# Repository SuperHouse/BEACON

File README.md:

IR / RF Transmitter / Receiver Beacon with WiFi
===============================================
Copyright 2016 SuperHouse Automation Pty Ltd  www.superhouse.tv  

Transmitter and receiver for both IR (infra-red) and 433MHz RF signals.
Includes a footprint for a Spark Core or Particle Photon.

Features:

 * Particle Photon controller
 * 433MHz transmitter
 * 433MHz receiver
 * I/R transmitter
 * I/R receiver
 * Status LEDs

More information:

  http://www.superhouse.tv/beacon

INSTALLATION
------------
The design is saved as an EAGLE project. EAGLE PCB design software is
available from www.cadsoftusa.com free for non-commercial use. To use
this project download it and place the directory containing these files
into the "eagle" directory on your computer. Then open EAGLE and
navigate to the project.

CREDITS
-------
Designed by Jonathan Oxer jon@oxer.com.au

DISTRIBUTION
------------
The specific terms of distribution of this project are governed by the
license referenced below.

LICENSE
-------
Licensed under the TAPR Open Hardware License (www.tapr.org/OHL).
The "license" folder within this repository also contains a copy of
this license in plain text format.

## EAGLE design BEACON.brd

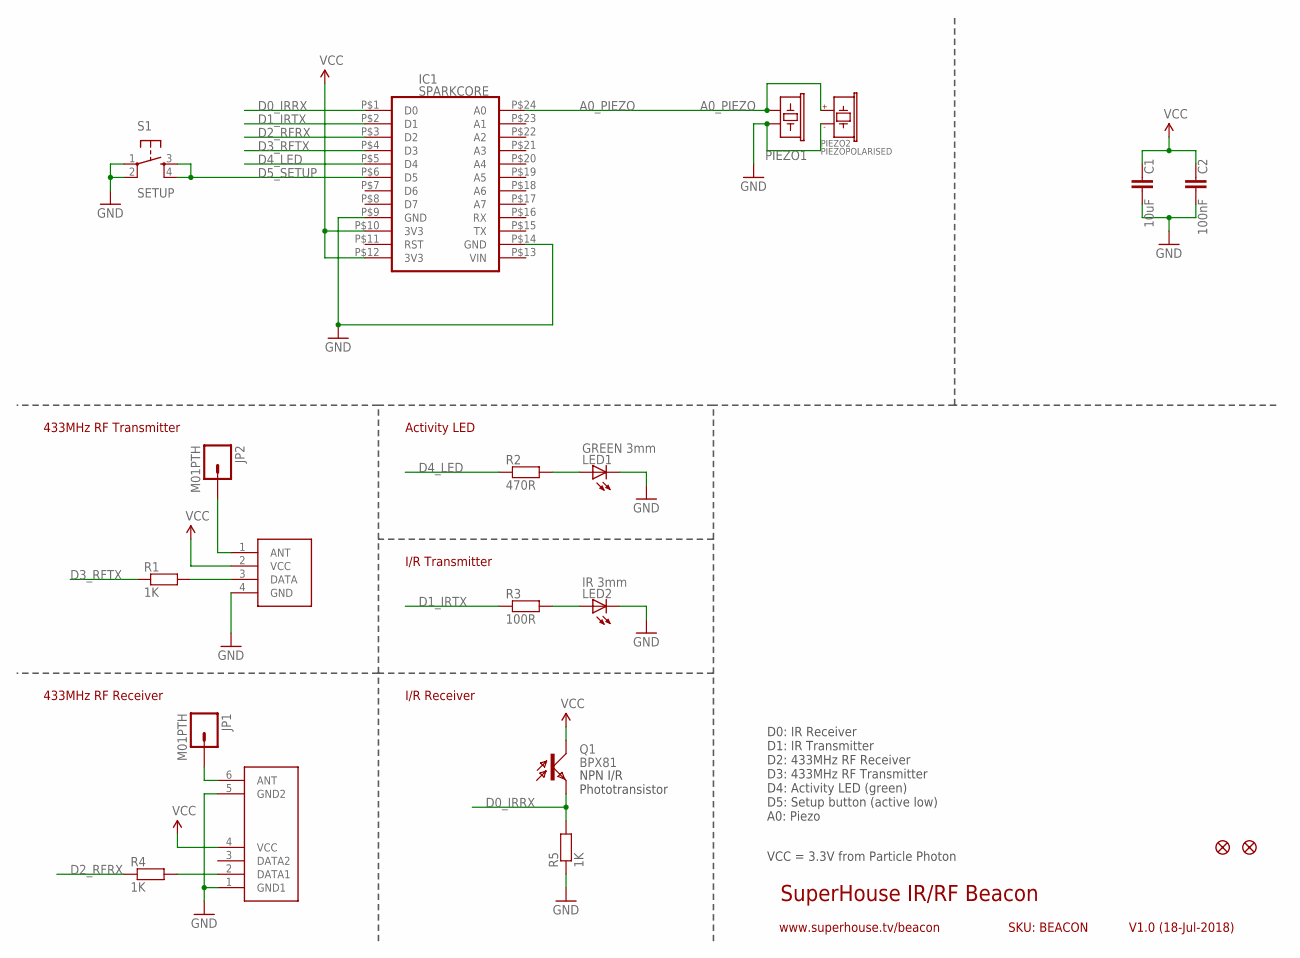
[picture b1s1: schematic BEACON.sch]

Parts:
C1: 10uF; C0805
C2: 100nF; 0603
IC1: SPARKCORE
IC2: TX-C1FLAT; TX-C1-FLAT
IC3: RXB1SHORTFLAT; RX-B1-SHORT-FLAT
JP1, JP2: M01PTH; 1X01
LED1: GREEN 3mm; LED3MM
LED2: IR 3mm; LED3MM
PIEZO1: BUZZERSMD12X12; BUZZER-12X12-SMT
PIEZO2: PIEZOPOLARISED; PIEZO12MMWIDEPOLARISED
Q1: BPX81
R1, R4, R5: 1K; 0603
R2: 470R; 0603
R3: 100R; 0603
S1: SETUP; TACTILE-PTH
U$4, U$5: FIDUCIAL1X2.5; FIDUCIAL-1X2.5

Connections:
A0_PIEZO: IC1.P$24 (A0), PIEZO1.1, PIEZO2.1 (+)
D0_IRRX: IC1.P$1 (D0), Q1.E, R5.2
D1_IRTX: IC1.P$2 (D1), R3.1
D2_RFRX: IC1.P$3 (D2), R4.1
D3_RFTX: IC1.P$4 (D3), R1.1
D4_LED: IC1.P$5 (D4), R2.1
D5_SETUP: IC1.P$6 (D5), S1.3, S1.4
GND: C1.1, C2.2, IC1.P$9 (GND), IC1.P$14 (GND), IC2.4 (GND), IC3.1 (GND1), IC3.5 (GND2), LED1.K (C), LED2.K (C), PIEZO1.2, PIEZO2.2 (-), R5.1, S1.1, S1.2
unnamed: LED1.A, R2.2
unnamed: IC2.3 (DATA), R1.2
unnamed: LED2.A, R3.2
unnamed: IC2.1 (ANT), JP2.1
unnamed: IC3.6 (ANT), JP1.1
unnamed: IC3.2 (DATA1), R4.2
VCC: C1.2, C2.1, IC1.P$10 (3V3), IC1.P$12 (3V3), IC2.2 (VCC), IC3.4 (VCC), Q1.C

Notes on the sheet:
SuperHouse IR/RF Beacon
SKU: BEACON
V1.0 (18-Jul-2018)
www.superhouse.tv/beacon
D0: IR Receiver D1: IR Transmitter D2: 433MHz RF Receiver D3: 433MHz RF Transmitter D4: Activity LED (green) D5: Setup button (active low) A0: Piezo
433MHz RF Transmitter
433MHz RF Receiver
Activity LED
I/R Receiver
I/R Transmitter
VCC = 3.3V from Particle Photon
NPN I/R Phototransistor

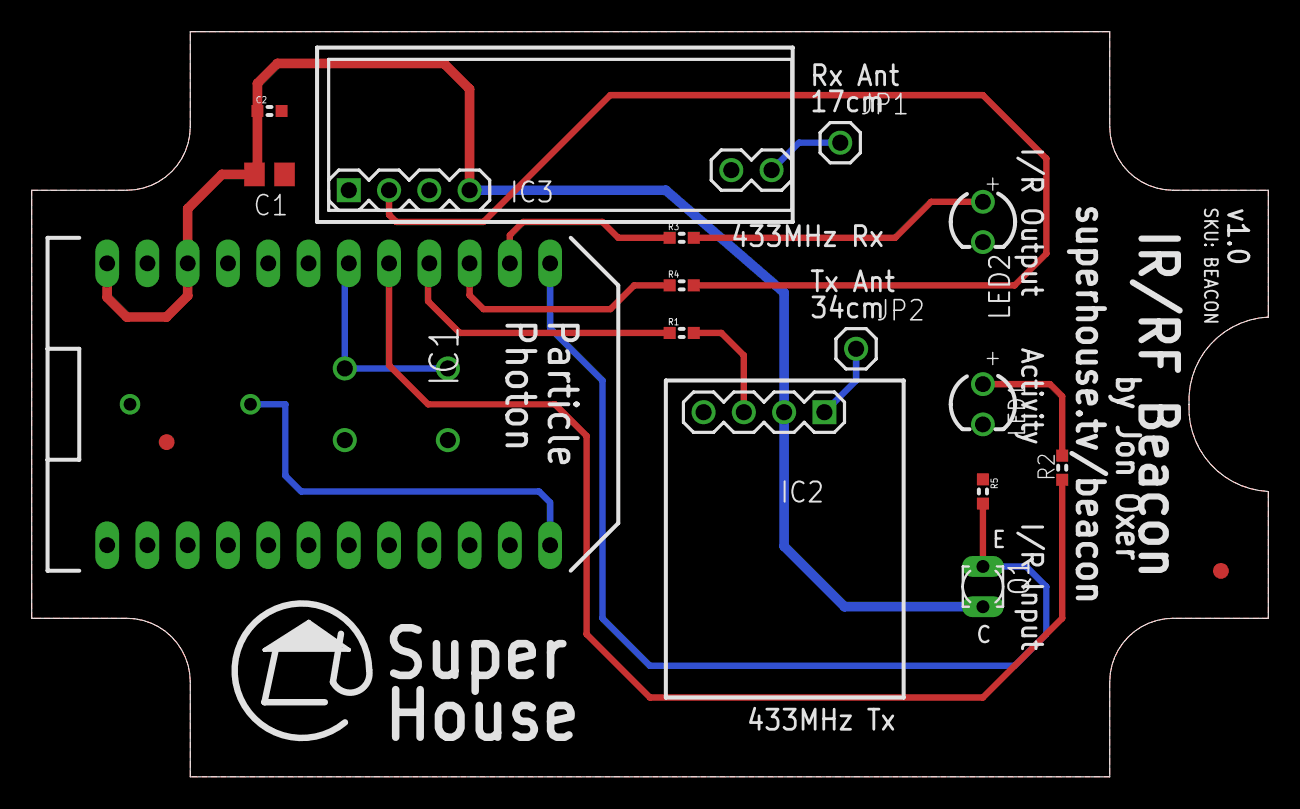
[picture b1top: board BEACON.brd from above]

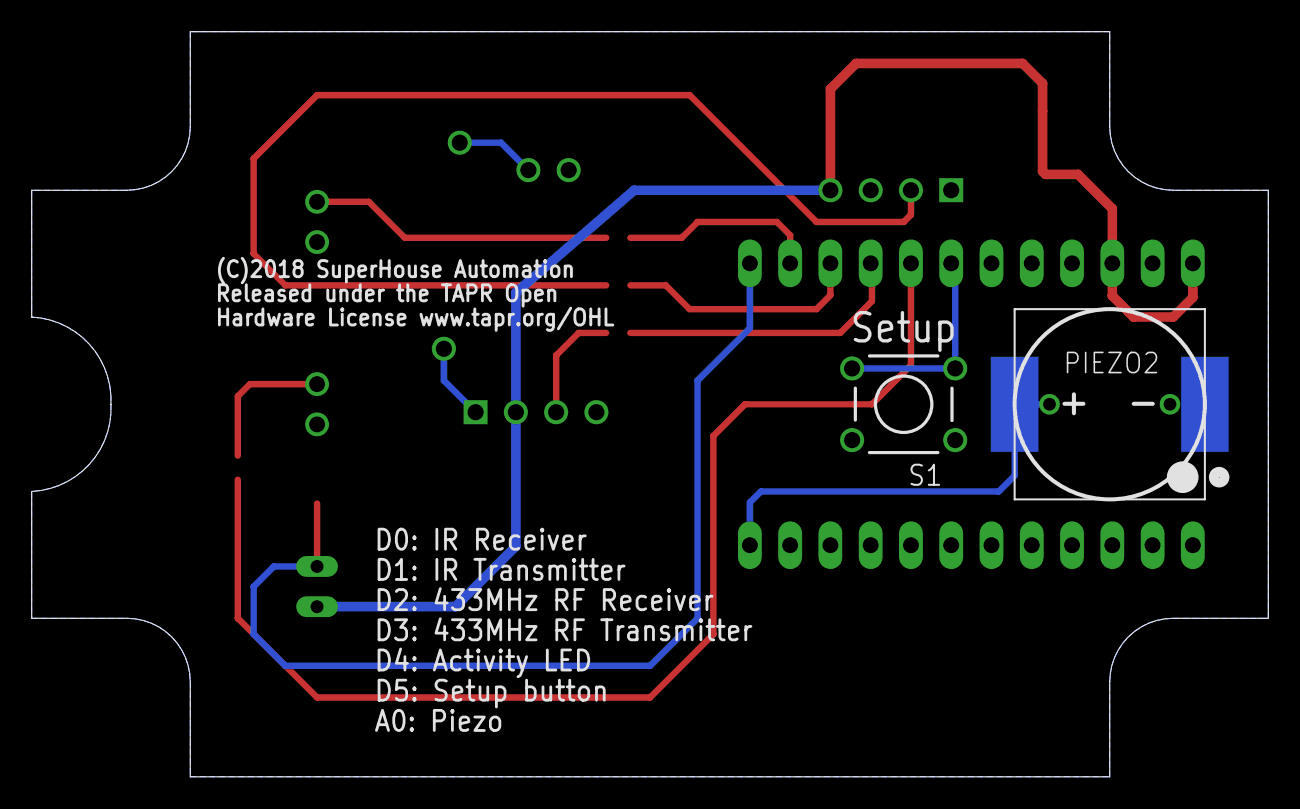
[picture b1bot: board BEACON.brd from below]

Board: 2 copper layers, 78.0 x 47.0 mm, 20 parts (3 on the bottom side), 15 nets.

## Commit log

2018-03-28 Initial import of project from Feb 2016
2018-07-17 Reduced PCB outline and added action button to initiate binding
2019-04-15 Added mechanical details

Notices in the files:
BEACON.brd:
(C)2018 SuperHouse Automation
